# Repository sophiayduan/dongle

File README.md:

# [Dongle](https://dongle.hackclub.com/)
**A [Hack Club](https://hackclub.com/) program from August 25-27th, 2026!**

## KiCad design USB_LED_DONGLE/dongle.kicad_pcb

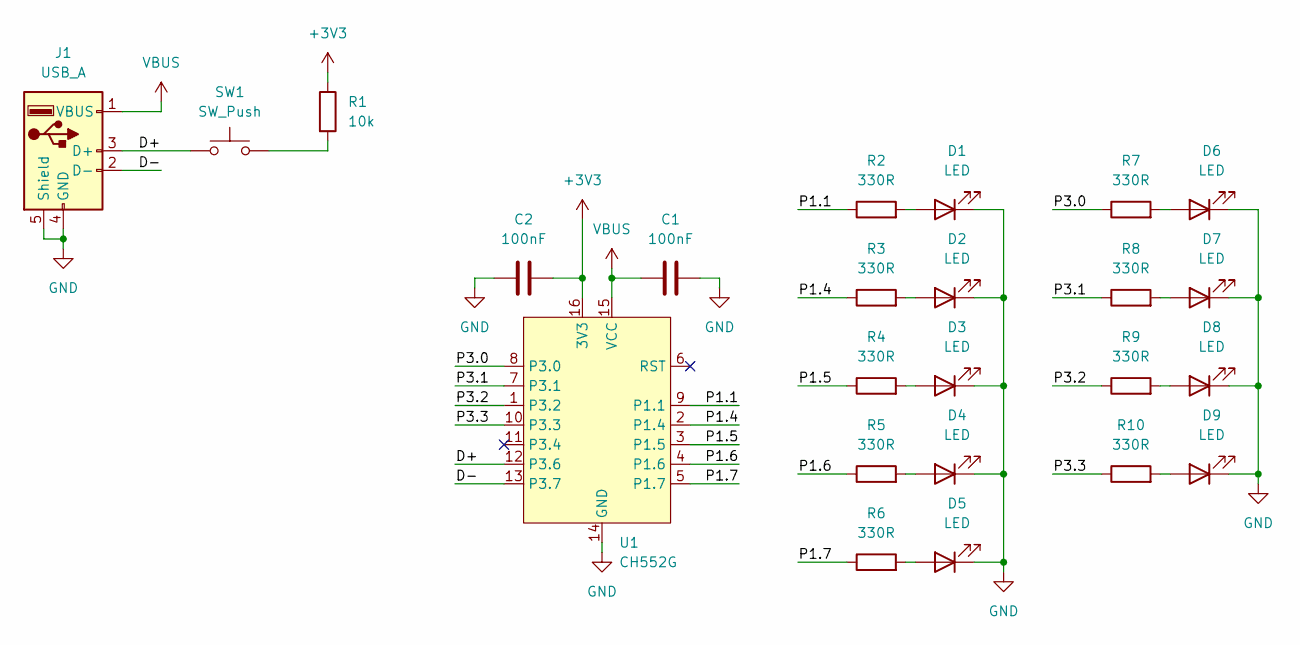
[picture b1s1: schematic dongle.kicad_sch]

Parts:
C1, C2: 100nF; C_0603_1608Metric
D1, D2, D3, D4, D5, D6, D7, D8, D9: LED; LED_0805_2012Metric
J1: USB_A; USB-A
R1: 10k; R_0603_1608Metric
R2, R3, R4, R5, R6, R7, R8, R9, R10: 330R; R_0603_1608Metric
SW1: SW_Push; SW_SPST_TS-1088-xR020
U1: CH552G

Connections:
+3V3: C2.2, R1.1, U1.16 (3V3)
/D+: J1.3 (D+), SW1.1, U1.12 (P3.6)
/D-: J1.2 (D-), U1.13 (P3.7)
/P1.1: R2.1, U1.9 (P1.1)
/P1.4: R3.1, U1.2 (P1.4)
/P1.5: R4.1, U1.3 (P1.5)
/P1.6: R5.1, U1.4 (P1.6)
/P1.7: R6.1, U1.5 (P1.7)
/P3.0: R7.1, U1.8 (P3.0)
/P3.1: R8.1, U1.7 (P3.1)
/P3.2: R9.1, U1.1 (P3.2)
/P3.3: R10.1, U1.10 (P3.3)
/P3.4: U1.11 (P3.4)
GND: C1.2, C2.1, D1.1 (K), D2.1 (K), D3.1 (K), D4.1 (K), D5.1 (K), D6.1 (K), D7.1 (K), D8.1 (K), D9.1 (K), J1.4 (GND), J1.5 (Shield), U1.14 (GND)
unnamed: D1.2 (A), R2.2
unnamed: D2.2 (A), R3.2
unnamed: D3.2 (A), R4.2
unnamed: D4.2 (A), R5.2
unnamed: D5.2 (A), R6.2
unnamed: D6.2 (A), R7.2
unnamed: D7.2 (A), R8.2
unnamed: D8.2 (A), R9.2
unnamed: D9.2 (A), R10.2
unnamed: R1.2, SW1.2
VBUS: C1.1, J1.1 (VBUS), U1.15 (VCC)

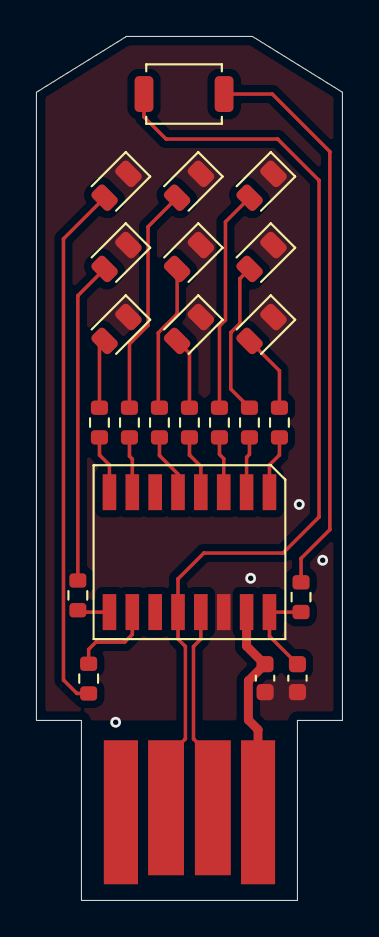
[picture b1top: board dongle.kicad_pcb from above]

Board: 2 copper layers, 17.0 x 48.0 mm, 24 parts (0 on the bottom side), 24 nets.

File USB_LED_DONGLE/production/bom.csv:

Designator,Footprint,Quantity,Value,LCSC Part #
"C1, C2",0603,2,100nF,
"D1, D2, D3, D4, D5, D6, D7, D8, D9",0805,9,LED,
J1,USB-A,1,USB_A,
R1,0603,1,10k,
"R10, R2, R3, R4, R5, R6, R7, R8, R9",0603,9,330R,
SW1,SW_SPST_TS-1088-xR020,1,SW_Push,
U1,CH552G,1,CH552G,
